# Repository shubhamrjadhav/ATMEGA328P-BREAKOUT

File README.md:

# ATMEGA328P-BREAKOUT
EAGLE design to create simple projects with atmega328p of arduino uno

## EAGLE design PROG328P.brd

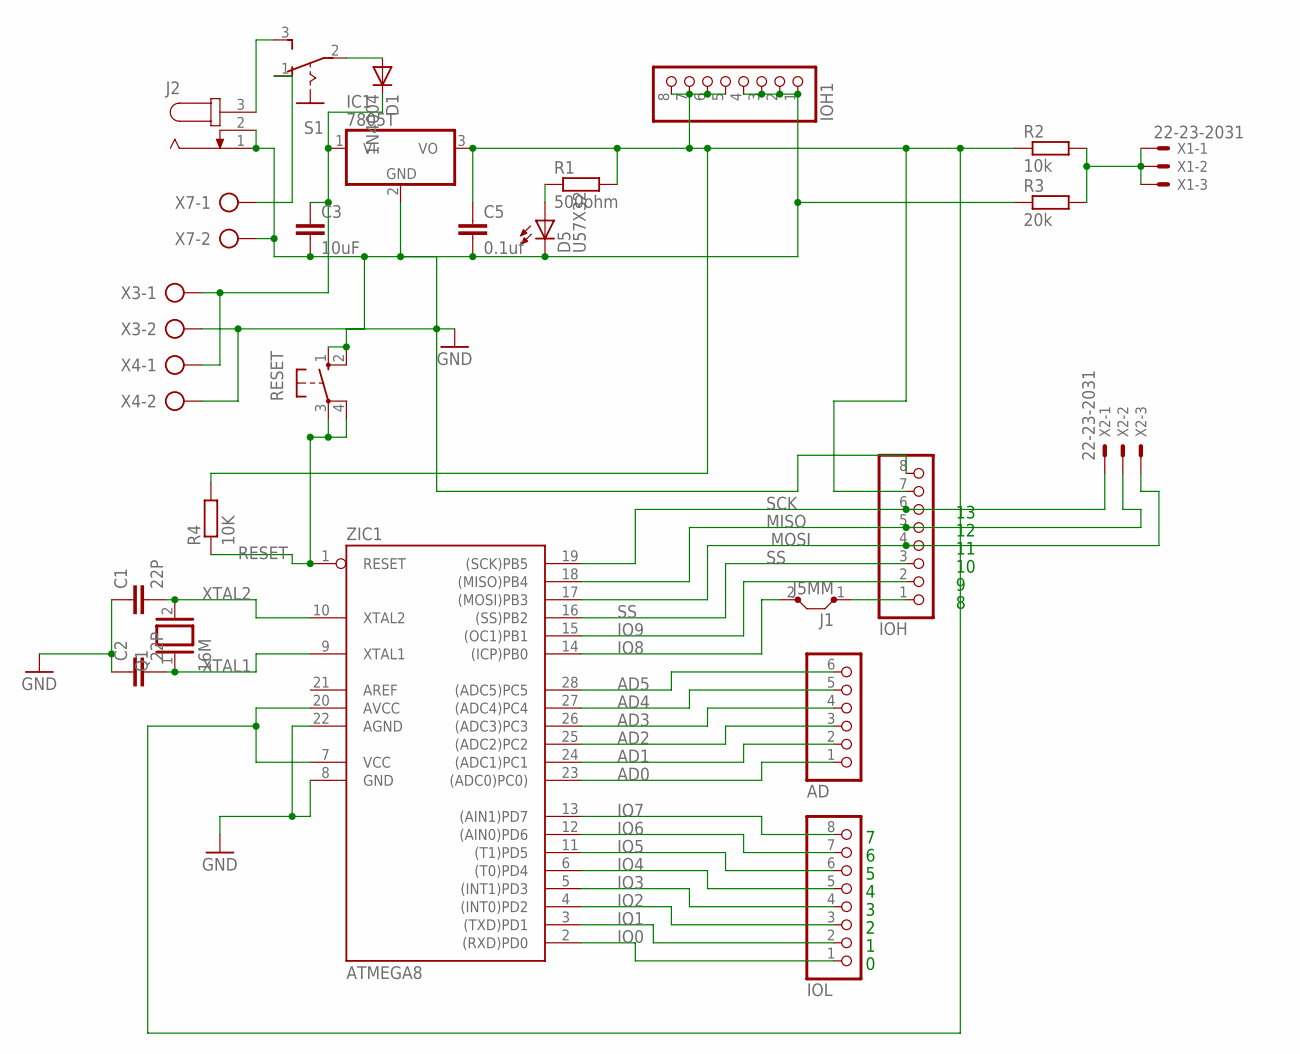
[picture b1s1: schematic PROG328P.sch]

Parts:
AD: PINHD-1X6; 1X06
C1, C2: 22P; C2.5-6
C3: 10uF; C2.5-4
C5: 0.1uf; C2.5-4
D1: 1N4004; DO41-10
D5: U57X32
IC1: 7805T; TO220H
IOH, IOH1: PINHD-1X8; 1X08
IOL: PINHD-1X8; 1X08
J1: J5MM; 05
J2: JACK-PLUG0; SPC4077
Q1: 16M; QS
R1: 500ohm; 0207/10
R2: 10k; 0207/10
R3: 20k; 0207/10
R4: 10K; 0207/10
RESET: 10-XX; B3F-10XX
S1: 255SB
X1, X2: 22-23-2031
X3, X4, X7: AK500/2-H
ZIC1: ATMEGA8; DIL28-3

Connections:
AD0: AD.1, ZIC1.23 ((ADC0)PC0))
AD1: AD.2, ZIC1.24 ((ADC1)PC1)
AD2: AD.3, ZIC1.25 ((ADC2)PC2)
AD3: AD.4, ZIC1.26 ((ADC3)PC3)
AD4: AD.5, ZIC1.27 ((ADC4)PC4)
AD5: AD.6, ZIC1.28 ((ADC5)PC5)
GND: C1.1, C2.1, C3.2, C5.2, D5.K (C), IC1.2 (GND), IOH.8, IOH1.1, IOH1.2, IOH1.3, IOH1.4, J2.1, J2.2, R3.1, RESET.1 (S), RESET.2 (S1), X3.2, X4.2, X7.2, ZIC1.8 (GND), ZIC1.22 (AGND)
IO0: IOL.1, ZIC1.2 ((RXD)PD0)
IO1: IOL.2, ZIC1.3 ((TXD)PD1)
IO2: IOL.3, ZIC1.4 ((INT0)PD2)
IO3: IOL.4, ZIC1.5 ((INT1)PD3)
IO4: IOL.5, ZIC1.6 ((T0)PD4)
IO5: IOL.6, ZIC1.11 ((T1)PD5)
IO6: IOL.7, ZIC1.12 ((AIN0)PD6)
IO7: IOL.8, ZIC1.13 ((AIN1)PD7)
IO8: J1.2, ZIC1.14 ((ICP)PB0)
IO9: IOH.2, ZIC1.15 ((OC1)PB1)
MISO: IOH.5, X2.2, ZIC1.18 ((MISO)PB4)
MOSI: IOH.4, X2.3, ZIC1.17 ((MOSI)PB3)
unnamed: IOH.1, J1.1
unnamed: D5.A, R1.1
unnamed: J2.3, S1.3 (S)
unnamed: S1.1 (O), X7.1
unnamed: R2.2, R3.2, X1.1, X1.2, X1.3
unnamed: D1.A, S1.2
unnamed: C3.1, D1.C, IC1.1 (VI), X3.1, X4.1
RESET: R4.1, RESET.3, RESET.4 (P1), ZIC1.1 (RESET)
SCK: IOH.6, X2.1, ZIC1.19 ((SCK)PB5)
SS: IOH.3, ZIC1.16 ((SS)PB2)
VCC: C5.1, IC1.3 (VO), IOH.7, IOH1.5, IOH1.6, IOH1.7, IOH1.8, R1.2, R2.1, R4.2, ZIC1.7 (VCC), ZIC1.20 (AVCC)
XTAL1: C2.2, Q1.1, ZIC1.9 (XTAL1)
XTAL2: C1.2, Q1.2, ZIC1.10 (XTAL2)

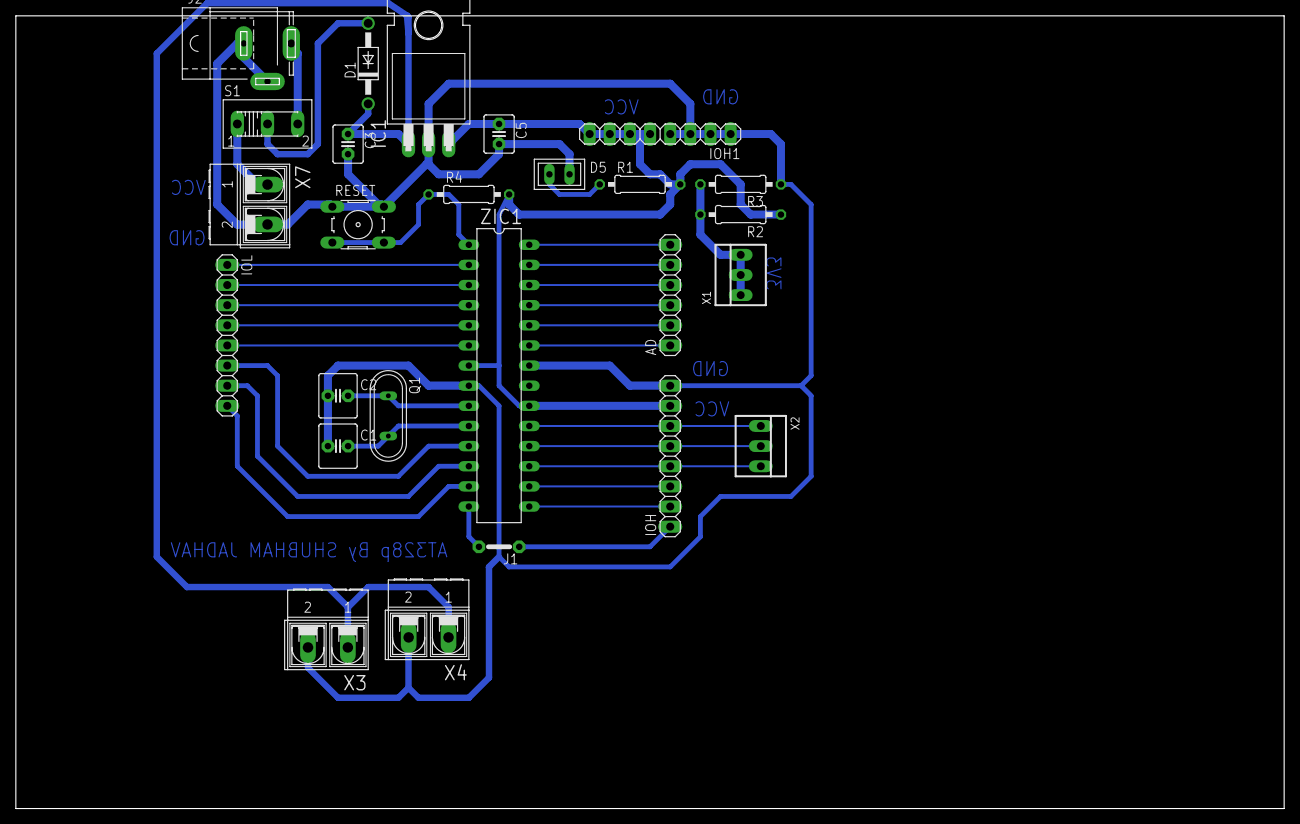
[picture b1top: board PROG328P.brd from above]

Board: 2 copper layers, 160.0 x 100.0 mm, 26 parts (0 on the bottom side), 32 nets.

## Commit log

2018-02-10 open this in eagle and give it for printing or print it at home
